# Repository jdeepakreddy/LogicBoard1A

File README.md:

## Full Documentation

I will amend this documentation as the project progresses.

**Logic Board 1 Variants:**

- Logic Board 1A (WiFi + BLE 5.0)
	- LB1A_DCA7M4_R512MB_F4GB (Dual Core A7 + M4, 512MB DDR3L RAM, 4GB eMMC)
	- LB1A_SCA7M4_R512MB_F4GB (Single Core A7 + M4, 512MB DDR3L RAM, 4GB eMMC)
- Logic Board 1B (Only WiFi)
	- LB1B_DCA7M4_R512MB_F4GB (Dual Core A7 + M4, 512MB DDR3L RAM, 4GB eMMC)
	- LB1B_SCA7M4_R512MB_F4GB (Single Core A7 + M4, 512MB DDR3L RAM, 4GB eMMC)
- Logic Board 1C (Only BLE 5.0)
	- LB1C_DCA7M4_R512MB_F4GB (Dual Core A7 + M4, 512MB DDR3L RAM, 4GB eMMC)
	- LB1C_SCA7M4_R512MB_F4GB (Single Core A7 + M4, 512MB DDR3L RAM, 4GB eMMC)
- Logic Board 1D (No wireless)
	- LB1D_DCA7M4_R512MB_F4GB (Dual Core A7 + M4, 512MB DDR3L RAM, 4GB eMMC)
	- LB1D_SCA7M4_R512MB_F4GB (Single Core A7 + M4, 512MB DDR3L RAM, 4GB eMMC)

**Logic Board I/O:**

Common expansion Board for all Logic Board 1 Variants. 

## A little background about the project

How it all started.

### Problem

While I was working on couple of popular linux dev boards like the BeagleBone Black and the Raspberry Pi, I've faced a few bunch of problems with both of them. Ofcourse, they are both fantastic boards to work with and they both have good community support, but, I are missing few things:

- **Raspberry Pi Compute Module 4 + IO Board**
    - CM4 is easy to use but not ideal for mass production.
    - No support for analog signals at hardware level.
    - Software PWM possible but not very precise.
    - Cannot support real time application or processing.
    - Not fully open-source and very minimum customization possible. <br>
<br>

- **BeagleBone Black**
    - Easy to use but user has to own build hardware for production.
    - PRUs make RT applications possible but super difficult to use.
    - Cannot support MIPI-DSI and HD graphics.
    - Programming PRUs is not an easy task.

### Solution

**Best of both worlds**

**Hello World STM32MP1 !!**

- Board design inspired from Raspberry Pi Compute Module 4 and CM4 IO board.
- Operating system derived from Beaglebone Black with implementation of Bonescript Library and Cloud9 IDE.
- Footprint compatible Single or dual Cortex-A7 Processors + dedicated Cortex-M4 core for real-time and low-power applications.
- Support for MIPI-DSI display for HMI applications.
- Fully open-source Hardware and Software.

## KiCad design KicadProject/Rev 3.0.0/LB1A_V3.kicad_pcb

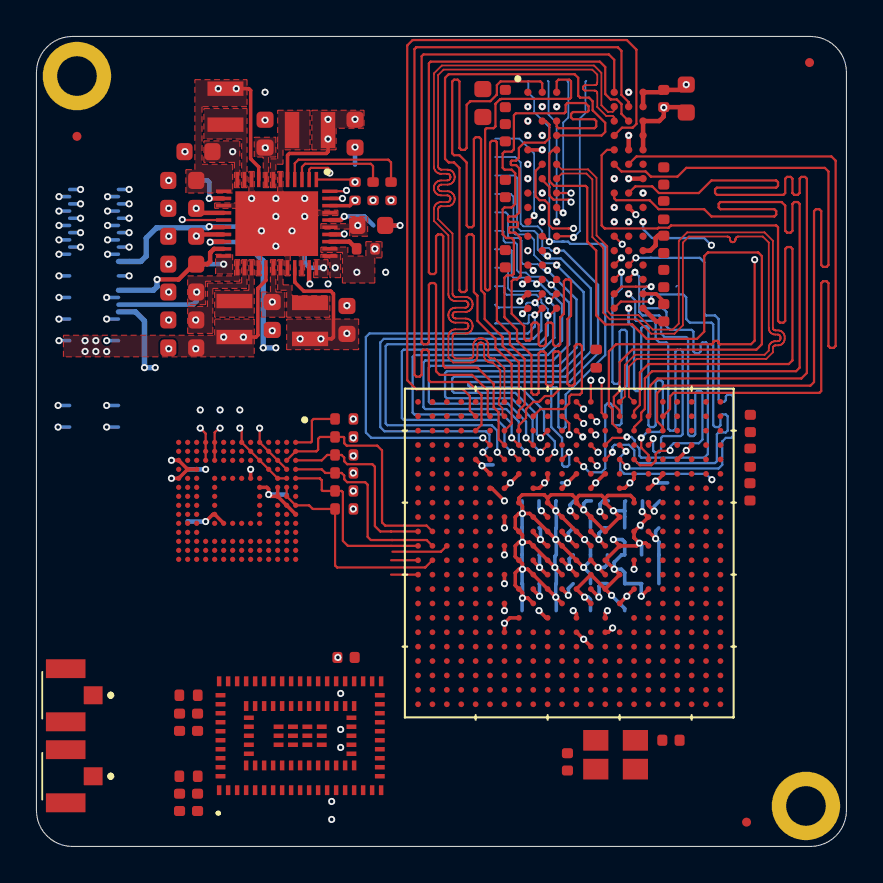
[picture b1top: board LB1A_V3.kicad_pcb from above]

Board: 6 copper layers, 45.0 x 45.0 mm, 188 parts (0 on the bottom side), 284 nets.

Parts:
C101, C105: 10nF; C_0402_1005Metric
C102, C103, C104: 10pF; C_0402_1005Metric
C201, C202, C203, C205, C206, C207, C208, C209, C210, C211, C212, C213, C214, C215, C216, C217, C218, C220, C221, C225, C226, C227, C228, C317, C325, C336, C337, C501, C502, C503, C504, C601, C607, C609: 100nF; C_0402_1005Metric
C223, C224, C401, C402, C403, C404, C405, C406, C407, C408, C412, C413, C414, C415, C416, C417: 10uF; C_0603_1608Metric
C229, C230, C409, C418, C419, C420, C421: 22uF; C_0603_1608Metric
C301, C302, C303, C304, C305, C306, C307, C308, C309, C310, C311, C312, C313, C314, C315, C316, C321, C322, C323, C324, C326, C327, C328, C329, C330, C331, C332, C333, C334, C335, C338, C339, C340, C341, C342: 1uF; C_0402_1005Metric
C410, C505, C506, C507, C606, C608: 4.7uF; C_0402_1005Metric
C411: 1uF; C_0603_1608Metric
C508: 2.2uF; C_0402_1005Metric
C602, C603, C604, C605: DNF; C_0402_1005Metric
FID701, FID702, FID703, FID704, FID705, FID706: Fiducial; Fiducial_0.5mm_Mask1.5mm
H701, H702: MountingHole_Pad; MountingHole_2.2mm_M2_DIN965_Pad
J601, J602: 2337019-1; 23370191
L401, L402, L403, L404: 1uH; MGV2520101R0M-10
R101: 3k; R_0402_1005Metric
R104, R105: 1k5; R_0402_1005Metric
R106, R221, R222, R501, R502, R503, R504, R505, R506, R507, R508, R509, R510, R603, R604, R605, R606, R607: 10k; R_0402_1005Metric
R201, R210: 240E; R_0402_1005Metric
R202, R203, R204, R205, R206, R207, R208, R209, R211, R212, R213, R214, R215, R216, R217, R218, R219, R220, R223, R224, R225, R227, R228, R229: 56E; R_0402_1005Metric
R226: 100E; R_0402_1005Metric
R301, R608: DNF; R_0402_1005Metric
R302, R401, R402, R601, R602: 0E; R_0402_1005Metric
U101: STM32MP157CAA3
U201: AS4C256M16D3LC-12BCN
U401: STPMIC1xPQR; STPMIC1BPQR
U501: S40FC004C1B2C00000
U601: LBEE59B1LV-278; LBEE59B1LV278
U701: DF40C-70DP-0.4V(51); DF40C70DP04V51
U702, U703: DF40C-100DP-0.4V(51); DF40C100DP04V51
X101: 32.768kHz; SiT1533AC-H5-DCC-32.768E
Y101: 24MHz; TSX3225240000MF10ZC3

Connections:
5V_VIN: C401.1, C402.1, C403.1, C404.1, C406.1, C407.1, C408.1, R401.2, R402.2, U401.8, U401.12, U401.19, U401.22, U401.24, U401.28, U401.36, U702.83, U702.84, U702.85, U702.86, U702.89, U702.90, U702.91, U702.92, U702.95, U702.96, U702.97, U702.98
/HSE_IN: C102.2, U101.T1, Y101.1
/HSE_OUT: C103.2, U101.T2, Y101.3
/LSE_IN: C104.1, U101.P1, X101.3
/MPU_DDR3L_Memory/DDR_A0: R202.2, U101.K19, U201.N3
/MPU_DDR3L_Memory/DDR_A1: R203.2, U101.M18, U201.P7
/MPU_DDR3L_Memory/DDR_A2: R204.2, U101.J18, U201.P3
/MPU_DDR3L_Memory/DDR_A3: R205.2, U101.J19, U201.N2
/MPU_DDR3L_Memory/DDR_A4: R206.2, U101.T18, U201.P8
/MPU_DDR3L_Memory/DDR_A5: R207.2, U101.H19, U201.P2
/MPU_DDR3L_Memory/DDR_A6: R208.2, U101.U19, U201.R8
/MPU_DDR3L_Memory/DDR_A7: R209.2, U101.F18, U201.R2
/MPU_DDR3L_Memory/DDR_A8: R211.2, U101.U18, U201.T8
/MPU_DDR3L_Memory/DDR_A9: R212.2, U101.H18, U201.R3
/MPU_DDR3L_Memory/DDR_A10: R213.2, U101.N18, U201.L7
/MPU_DDR3L_Memory/DDR_A11: R214.2, U101.P19, U201.R7
/MPU_DDR3L_Memory/DDR_A12: R215.2, U101.N19, U201.N7
/MPU_DDR3L_Memory/DDR_A13: R216.2, U101.G18, U201.T3
/MPU_DDR3L_Memory/DDR_A14: R217.2, U101.P18, U201.T7
/MPU_DDR3L_Memory/DDR_BA0: R218.2, U101.K20, U201.M2
/MPU_DDR3L_Memory/DDR_BA1: R219.2, U101.R18, U201.N8
/MPU_DDR3L_Memory/DDR_BA2: R220.2, U101.K18, U201.M3
/MPU_DDR3L_Memory/DDR_CASN: R225.2, U101.M22, U201.K3
/MPU_DDR3L_Memory/DDR_CKE: R222.2, R227.2, U101.R19, U201.K9
/MPU_DDR3L_Memory/DDR_CLK_N: R226.1, U101.N21, U201.K7
/MPU_DDR3L_Memory/DDR_CLK_P: R226.2, U101.N20, U201.J7
/MPU_DDR3L_Memory/DDR_CSN: R228.2, U101.L18, U201.L2
/MPU_DDR3L_Memory/DDR_DQ0: U101.E21, U201.D7
/MPU_DDR3L_Memory/DDR_DQ1: U101.F21, U201.A7
/MPU_DDR3L_Memory/DDR_DQ2: U101.H21, U201.A3
/MPU_DDR3L_Memory/DDR_DQ3: U101.E20, U201.B8
/MPU_DDR3L_Memory/DDR_DQ4: U101.J21, U201.C2
/MPU_DDR3L_Memory/DDR_DQ5: U101.H20, U201.C3
/MPU_DDR3L_Memory/DDR_DQ6: U101.H22, U201.A2
/MPU_DDR3L_Memory/DDR_DQ7: U101.G19, U201.C8
/MPU_DDR3L_Memory/DDR_DQ8: U101.N22, U201.F2
/MPU_DDR3L_Memory/DDR_DQ9: U101.R21, U201.E3
/MPU_DDR3L_Memory/DDR_DQ10: U101.P21, U201.G2
/MPU_DDR3L_Memory/DDR_DQ11: U101.T20, U201.H7
/MPU_DDR3L_Memory/DDR_DQ12: U101.V20, U201.F7
/MPU_DDR3L_Memory/DDR_DQ13: U101.R20, U201.H3
/MPU_DDR3L_Memory/DDR_DQ14: U101.U21, U201.H8
/MPU_DDR3L_Memory/DDR_DQ15: U101.V21, U201.F8
/MPU_DDR3L_Memory/DDR_DQM0: U101.G20, U201.D3
/MPU_DDR3L_Memory/DDR_DQM1: U101.T21, U201.E7
/MPU_DDR3L_Memory/DDR_DQS0_N: U101.G21, U201.B7
/MPU_DDR3L_Memory/DDR_DQS0_P: U101.G22, U201.C7
/MPU_DDR3L_Memory/DDR_DQS1_N: U101.R22, U201.G3
/MPU_DDR3L_Memory/DDR_DQS1_P: U101.T22, U201.F3
/MPU_DDR3L_Memory/DDR_ODT: R224.2, U101.L21, U201.K1
/MPU_DDR3L_Memory/DDR_RASN: R223.2, U101.M20, U201.J3
/MPU_DDR3L_Memory/DDR_RESETN: R221.2, U101.F19, U201.T2
/MPU_DDR3L_Memory/DDR_WEN: R229.2, U101.M21, U201.L3
ANA0: U101.R4, U703.84
ANA1: U101.T5, U703.83
BOOT0: U101.N3, U703.32
BOOT1: U101.N4, U703.33
BOOT2: U101.P4, U703.34
BT_DEV_WAKE: U101.H3, U601.29
BT_HOST_WAKE: U101.A2, U601.5
BT_PCM_CLK: U101.G2, U601.85
BT_PCM_SDI: U101.H5, U601.82
BT_PCM_SDO: U101.K5, U601.84
BT_PCM_WS: U101.F4, U601.83
BT_REG_ON: U101.G3, U601.9
BT_RF_OUT: C602.1, R601.2, U601.49
BT_USART3_CTS: U101.W1, U601.33
BT_USART3_RTS: U101.W12, U601.34
BT_USART3_RX: U101.AA7, U601.31
BT_USART3_TX: U101.V9, U601.32
DSI_CK_N: U101.A16, U703.95
DSI_CK_P: U101.B16, U703.96
DSI_D0_N: U101.A15, U703.99
DSI_D0_P: U101.B15, U703.100
DSI_D1_N: U101.A17, U703.97
DSI_D1_P: U101.B17, U703.98
GND: C101.2, C102.1, C103.1, C104.2, C105.2, C201.2, C202.2, C203.2, C205.2, C206.2, C207.2, C208.2, C209.2, C210.2, C211.2, C212.2, C213.2, C214.2, C215.2, C216.2, C217.2, C218.2, C220.2, C221.2, C223.2, C224.2, C225.2, C226.2, C227.2, C228.2, C229.2, C230.2, C301.2, C302.2, C303.2, C304.2, C305.2, C306.2, C307.2, C308.2, C309.2, C310.2, C311.2, C312.2, C313.2, C314.2, C315.2, C316.2, C317.2, C321.2, C322.2, C323.2, C324.2, C325.1, C326.2, C327.2, C328.2, C329.2, C330.2, C331.2, C332.2, C333.2, C334.2, C335.2, C336.2, C337.2, C338.2, C339.2, C340.2, C341.2, C342.2, C401.2, C402.2, C403.2, C404.2, C405.2, C406.2, C407.2, C408.2, C409.1, C410.2, C411.1, C412.1, C413.1, C414.1, C415.1, C416.1, C417.1, C418.2, C419.2, C420.2, C421.2, C501.2, C502.2, C503.2, C504.2, C505.2, C506.2, C507.2, C508.2, C601.2, C602.2, C603.2, C604.2, C605.2, C606.2, C607.2, C608.2, C609.2, H701.1, H702.1, J601.2, J601.3, J602.2, J602.3, R101.2, R201.2, R210.2, R221.1, R222.1, U101.A1, U101.A19, U101.A22, U101.AA4, U101.AA12, U101.AA13, U101.AA16, U101.AA18, U101.AB1, U101.AB18, U101.AB22, U101.B2, U101.B19, U101.C3, U101.C8, U101.C11, U101.C14, U101.C15, U101.C16, U101.C17, U101.C18, U101.C19, U101.C20, U101.D4, U101.D19, U101.E5, U101.E19, U101.F6, U101.F7, U101.F8, U101.F16, U101.F20, U101.G4, U101.G6, U101.G8, U101.G10, U101.G12, U101.G14, U101.G17, U101.H7, U101.J9, U101.J11, U101.J13, U101.J17, U101.J20, U101.K3, U101.K7, U101.K10, U101.K12, U101.K14, U101.L9, U101.L11, U101.L13, U101.L17, U101.L19, U101.L20, U101.M5, U101.M7, U101.M10, U101.M12, U101.M14, U101.N6, U101.N9, U101.N11, U101.N13, U101.N17, U101.P2, U101.P3, U101.P5, U101.P7, U101.P10, U101.P12, U101.P14, U101.P20, U101.R6, U101.R8, U101.R17, U101.T6, U101.T7, U101.T9, U101.T11, U101.T19, U101.U6, U101.U7, U101.U13, U101.U15, U101.U17, U101.U20, U101.V5, U101.V16, U101.V18, U101.V19, U101.W17, U101.W19, U101.Y3, U101.Y7, U101.Y10, U101.Y13, U101.Y14, U101.Y15, U101.Y18, U101.Y20, U201.A9, U201.B1, U201.B3, U201.B9, U201.D1, U201.D8, U201.E1, U201.E2, U201.E8, U201.F9, U201.G1, U201.G8, U201.G9, U201.J2, U201.J8, U201.M1, U201.M9, U201.P1, U201.P9, U201.T1, U201.T9, U401.6, U401.10, U401.15, U401.26, U401.30, U401.32, U401.41, U401.ep, U501.A6, U501.C4, U501.D3, U501.E2, U501.E7, U501.F1, U501.G5, U501.H10, U501.J5, U501.K8, U501.N2, U501.N5, U501.P1, U501.P4, U501.P6, U601.1, U601.2, U601.3, U601.6, U601.11, U601.15, U601.19, U601.20, U601.27, U601.30, U601.36, U601.47, U601.48, U601.50, U601.51, U601.52, U601.53, U601.57, U601.59, U601.60, U601.65, U601.72, U601.73, U601.94, U601.95, U601.96, U601.97, U601.98, U601.99, U601.100, U601.101, U601.102, U601.103, U601.104, U601.105, U601.106, U702.33, U702.34, U702.39, U702.40, U702.57, U702.58, U702.63, U702.64, U702.69, U702.70, U702.75, U702.76, U702.81, U702.82, U702.87, U702.88, U702.93, U702.94, U702.99, U702.100, X101.2, Y101.2, Y101.4
I2C4_SCL: R104.1, U101.G1, U401.4, U703.86
I2C4_SDA: R105.1, U101.H4, U401.3, U703.85
JTDI: U101.D16, U701.43
JTDO_TRACESWO: U101.E16, U701.42
JTRST: U101.E15, U701.41
LPO_32: U101.AB10, U601.80
MPU_VDDA_1V8_REG: C335.1, C336.1, U101.AB12, U101.B14
NRST: C101.1, R106.1, U101.R2, U401.1, U501.J1, U501.J2, U501.J3, U501.K5, U703.82
unnamed: C105.1, U101.R1
unnamed: C317.1, R301.1, R302.1, U101.M4
unnamed: C330.1, U101.AB17
unnamed: C342.1, U101.A18, U101.B18
unnamed: C409.2, U401.34
unnamed: C410.1, U401.40
unnamed: C508.1, U501.C1, U501.C2
unnamed: C603.1, J601.1, R601.1
unnamed: C604.1, R602.2, U601.58
unnamed: C605.1, J602.1, R602.1
unnamed: L401.1, U401.7
unnamed: L402.1, U401.11
unnamed: L403.1, U401.29
unnamed: L404.1, U401.25
unnamed: R101.1, U101.AA17
unnamed: R201.1, U201.L8
unnamed: R210.1, U101.K22
unnamed: R401.1, U401.33
unnamed: R402.1, U401.37
OTG_VBUS: U101.V15, U701.24
PA0_WAKEUP: U101.AA3, U401.43
PA1: U101.V4, U701.1
PA2: U101.AB2, U701.2
PA3: U101.T4, U701.3
PA4: U101.V6, U701.4
PA5: U101.U5, U701.5
PA6: U101.W9, U701.6
PA7: U101.Y9, U701.7
PA10: U101.Y17, U701.8
PA11: U101.Y16, U701.9
PA12: U101.W16, U701.10
PA13: U101.W3, U701.11
PA14: U101.R3, U701.12
PA15: U101.E11, U701.13
PB0: U101.AB5, U701.14
PB1: U101.AA5, U701.15
PB2: U101.V13, U701.16
PB5: U101.AA8, U701.17
PB6: U101.W13, U701.18
PB7: U101.F11, U701.19
PB8: U101.AB8, U701.20
PB9: U101.F12, U701.21
PB11: U101.Y5, U701.22
PB13: U101.V10, U701.23
PC0: U101.U10, U701.70
PC1: U101.AB3, U701.69
PC2: U101.Y1, U701.68
PC3: U101.U3, U701.67
PC4: U101.AB6, U701.66
PC5: U101.AA6, U701.65
PC6: U101.E13, U701.64
PC7: U101.D13, U701.63
PD0: U101.C10, U701.57
PD1: U101.B10, U701.56
PD4: U101.C9, U701.54
PD5: U101.A9, U701.53
PD6: U101.L3, U701.52
PD8: U101.M1, U701.51
PD9: U101.M2, U701.50
PD10: U101.A8, U701.49
PD11: U101.AB9, U701.48
PD13: U101.V14, U701.47
PD14: U101.M3, U701.46
PE0: U101.C5, U702.1
PE1: U101.D7, U702.2
PE2: U101.Y2, U702.3
PE4: U101.F15, U702.4
PE6: U101.E9, U702.5
PE7: U101.W10, U702.6
PE8: U101.Y12, U702.7
PE9: U101.W11, U702.8
PE10: U101.W14, U702.9
PE11: U101.D5, U702.10
PE12: U101.E4, U702.11
PE13: U101.A4, U702.12
PE14: U101.B4, U702.13
PE15: U101.C4, U702.14
PF2: U101.F13, U702.15
PF3: U101.V3, U702.16
PF6: U101.AA11, U702.17
PF7: U101.AA10, U702.18
PF9: U101.AB11, U702.19
PF10: U101.V12, U702.20
PF11: U101.W8, U702.21
PF12: U101.V8, U702.22
PF13: U101.W7, U702.23
PF14: U101.V7, U702.24
PF15: U101.W6, U702.25
PG0: U101.W5, U703.80
PG1: U101.Y4, U703.70
PG2: U101.W4, U703.79
PG3: U101.U4, U703.69
PG4: U101.AB4, U703.78
PG5: U101.U8, U703.68
PG7: U101.Y11, U703.77
PG8: U101.Y8, U703.67
PG9: U101.W15, U703.76
PG10: U101.AA9, U703.66
PG11: U101.U11, U703.75
PG12: U101.J4, U703.65
PG13: U101.AA1, U703.74
PG14: U101.AA2, U703.64
PH2: U101.AB7, U703.73
PH3: U101.Y6, U703.56
PH6: U101.V11, U703.72
PH7: U101.W2, U703.63
PH8: U101.D6, U703.71
PH9: U101.E6, U703.55
PH10: U101.B1, U703.62
PH11: U101.B3, U703.61
PH12: U101.F5, U703.60
PH13: U101.D3, U703.59
PH14: U101.C2, U703.58
PH15: U101.C1, U703.57
PI0: U101.D1, U703.1
PI1: U101.E2, U703.2
PI2: U101.E1, U703.3
PI3: U101.E3, U703.4
PI4: U101.J6, U703.5
PI5: U101.F2, U703.6
PI6: U101.G5, U703.7
PI7: U101.F1, U703.8
PI8: U101.N1, U703.9
PI9: U101.J5, U703.10
PI11: U101.T3, U703.11
PI12: U101.H2, U703.12
PI13: U101.H1, U703.13
PI14: U101.D2, U703.14
PI15: U101.F3, U703.15
PJ0: U101.J2, U703.16
PJ1: U101.L6, U703.17
PJ2: U101.K4, U703.18
PJ3: U101.J1, U703.19
PJ4: U101.K2, U703.20
PJ5: U101.K1, U703.21
PJ6: U101.L5, U703.22
PJ7: U101.H6, U703.23
PJ8: U101.L4, U703.24
PJ9: U101.J3, U703.25
PJ10: U101.L2, U703.26
PJ11: U101.K6, U703.27
PJ12: U101.B8, U703.28
PJ13: U101.A7, U703.29
PJ14: U101.B7, U703.30
PJ15: U101.C7, U703.31
PK0: U101.D8, U703.94
PK1: U101.E7, U703.93
PK2: U101.E8, U703.92
PK3: U101.B6, U703.91
PK4: U101.A6, U703.90
PK5: U101.C6, U703.89
PK6: U101.A5, U703.88
PK7: U101.B5, U703.87
PMIC_LDO1_1V8: C413.2, C606.1, C607.1, C608.1, C609.1, R603.1, R604.1, R605.1, R606.1, R607.1, R608.1, U401.23, U601.13, U601.14, U601.35, U702.65, U702.66, U702.67, U702.68
PMIC_LDO2_2V9: C415.2, U401.18, U702.77, U702.78, U702.79, U702.80
PMIC_LDO3_VTT_DDR: C203.1, C205.1, C206.1, C208.1, C209.1, C210.1, C211.1, C225.1, C226.1, C227.1, C228.1, C229.1, C230.1, C412.2, R202.1, R203.1, R204.1, R205.1, R206.1, R207.1, R208.1, R209.1, R211.1, R212.1, R213.1, R214.1, R215.1, R216.1, R217.1, R218.1, R219.1, R220.1, R223.1, R224.1, R225.1, R227.1, R228.1, R229.1, U401.14
PMIC_LDO4_VDD_USB: C337.1, C417.2, U101.AB13, U101.AB16, U401.39
PMIC_LDO5_2V9: C416.2, C501.1, C502.1, C503.1, C504.1, C505.1, C506.1, C507.1, R501.1, R502.1, R503.1, R504.1, R505.1, R506.1, R507.1, R508.1, R509.1, R510.1, U401.20, U501.A9, U501.B8, U501.C6, U501.C7, U501.E6, U501.F5, U501.J10, U501.K9, U501.M4, U501.N4, U501.P3, U501.P5, U702.35, U702.36, U702.37, U702.38
PMIC_LDO6_1V0: C414.2, U401.21, U702.71, U702.72, U702.73, U702.74
PMIC_VOUT1_VDD_CORE: C305.1, C306.1, C307.1, C308.1, C313.1, C314.1, C315.1, C316.1, C321.1, C322.1, C323.1, C324.1, C326.1, C327.1, C328.1, C329.1, C418.1, L401.2, U101.H9, U101.H11, U101.H13, U101.H15, U101.J8, U101.J10, U101.J12, U101.J14, U101.K9, U101.K11, U101.K13, U101.K15, U101.L8, U101.L10, U101.L12, U101.L14, U101.M11, U101.M13, U101.M15, U101.N12, U101.N14, U101.P13, U101.P15, U101.R14, U101.T15, U401.5
PMIC_VOUT2_VDD_DDR: C212.1, C213.1, C214.1, C215.1, C216.1, C217.1, C218.1, C220.1, C221.1, C223.1, C224.1, C331.1, C332.1, C333.1, C334.1, C338.1, C339.1, C340.1, C341.1, C405.1, C419.1, L402.2, U101.E18, U101.F17, U101.G16, U101.H17, U101.J16, U101.K17, U101.L16, U101.M17, U101.N16, U101.P17, U101.R16, U101.T17, U101.U16, U101.V17, U101.W18, U101.Y19, U201.A1, U201.A8, U201.B2, U201.C1, U201.C9, U201.D2, U201.D9, U201.E9, U201.F1, U201.G7, U201.H2, U201.H9, U201.K2, U201.K8, U201.N1, U201.N9, U201.R1, U201.R9, U401.9, U401.13
PMIC_VOUT3_VDD: C301.1, C302.1, C303.1, C304.1, C309.1, C310.1, C311.1, C312.1, C420.1, L403.2, R104.2, R105.2, R106.2, R302.2, U101.A14, U101.D18, U101.M6, U101.M9, U101.N5, U101.N8, U101.N10, U101.P9, U101.P11, U101.R5, U101.R10, U101.R12, U101.T13, U101.U2, U101.U9, U101.U12, U101.U14, U101.V2, U401.31, U401.42, X101.4
PMIC_VOUT4_3V3: C421.1, L404.2, U401.27, U702.51, U702.52, U702.53, U702.54, U702.55, U702.56, U702.59, U702.60, U702.61, U702.62
PMIC_VREF_DDR: C201.1, C202.1, C207.1, C411.2, U101.AB19, U201.H1, U201.M8, U401.16
PMIC_WAKEUP: U101.N2, U401.2
PONKEYn: U401.17, U703.81
POWER_ON: U101.V1, U401.44
SDMMC1_CK: U101.E12, U701.58
SDMMC1_CMD: U101.D12, U701.55
SDMMC1_D0: U101.E14, U701.62
SDMMC1_D1: U101.D14, U701.61
SDMMC1_D2: U101.F14, U701.60
SDMMC1_D3: U101.D15, U701.59
SDMMC2_CK: R509.2, U101.A10, U501.K1, U501.K2, U501.K3, U501.M6
SDMMC2_CMD: R510.2, U101.D11, U501.L1, U501.L2, U501.L3, U501.M5
SDMMC2_D0: R501.2, U101.A13, U501.A3
SDMMC2_D1: R502.2, U101.B12, U501.A4
SDMMC2_D2: R503.2, U101.A12, U501.A5
SDMMC2_D3: R504.2, U101.C13, U501.A1, U501.B2
SDMMC2_D4: R505.2, U101.B13, U501.A2, U501.B3
SDMMC2_D5: R506.2, U101.A11, U501.B4, U501.C3, U501.D2, U501.E1
SDMMC2_D6: R507.2, U101.C12, U501.B5, U501.C5, U501.D4, U501.E3, U501.F2, U501.G1
SDMMC2_D7: R508.2, U101.B11, U501.A8, U501.B6, U501.B7
SDMMC3_CK: R606.2, U101.D10, U601.24
SDMMC3_CMD: R608.2, U101.B9, U601.26
SDMMC3_D0: R605.2, U101.E10, U601.23
SDMMC3_D1: R604.2, U101.F9, U601.22
SDMMC3_D2: R603.2, U101.D9, U601.21
SDMMC3_D3: R607.2, U101.F10, U601.25
STLINK_SWCLK: U101.D17, U701.44
STLINK_SWDIO: U101.E17, U701.45
USB1_N: U101.AB15, U701.25
USB1_P: U101.AA15, U701.26
USB2_N: U101.AA14, U701.27
USB2_P: U101.AB14, U701.28
VDDA: C325.2, U101.P6
VDDOUT_VDDIO: C601.1, U601.4, U601.28
WL_HOST_WAKE: U101.L1, U601.7
WL_REG_ON: U101.A3, U601.10

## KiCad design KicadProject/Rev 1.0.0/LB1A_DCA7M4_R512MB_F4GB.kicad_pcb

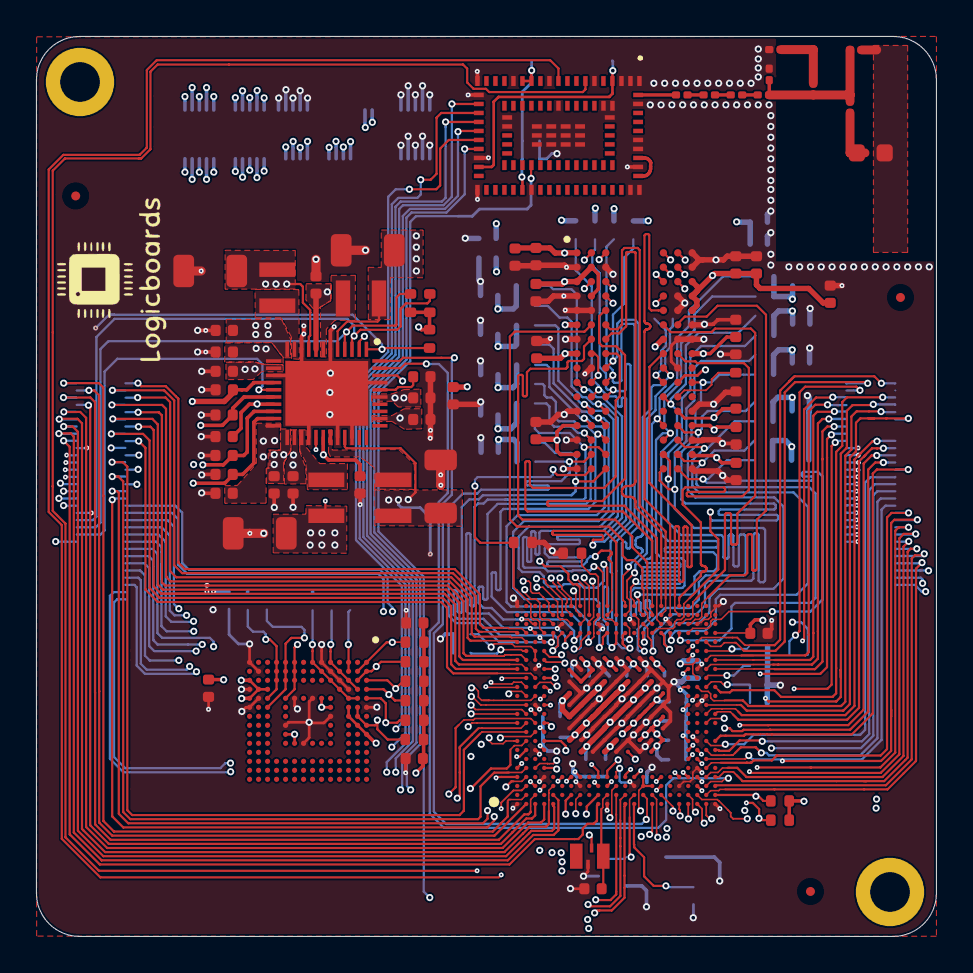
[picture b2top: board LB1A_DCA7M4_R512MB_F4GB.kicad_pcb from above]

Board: 6 copper layers, 50.0 x 50.0 mm, 156 parts (0 on the bottom side), 213 nets.

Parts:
C1, C2, C5, C6, C51, C52, C63, C64, C65, C66, C67, C68, C69, C70, C72, C73, C74: 1uF; C_0402_1005Metric
C3, C4, C8, C9, C10, C11, C12, C13, C14, C15, C16, C17, C18, C19, C20, C23, C24, C25, C26, C27, C28, C29, C30, C31, C32, C36, C37, C38, C39, C40, C79, C86: 100nF; C_0402_1005Metric
C7: 10nF; C_0402_1005Metric
C21, C22, C34, C35, C41, C43, C44, C45, C46, C54: 10uF; C_0402_1005Metric
C33: 0.3pF; C_0603_1608Metric
C42: 2.2uF; C_0402_1005Metric
C47, C48, C49, C50: 22uF; C_1206_3216Metric
C53, C55, C56, C57, C58, C59, C60, C61, C62, C85: 4.7uF; C_0402_1005Metric
C71: 0.3pF; C_0201_0603Metric
C75, C76, C77: 10pF; C_0402_1005Metric
C78: 2.0pF; C_0201_0603Metric
FID1, FID2, FID3, FID4, FID5, FID6: Fiducial; Fiducial_0.5mm_Mask1.5mm
H1, H3: MountingHole_Pad; MountingHole_2.2mm_M2_DIN965_Pad
L1, L2, L3, L4: 1uH; MGV2520101R0M-10
L5: 1.0nH; L_0201_0603Metric
L6: 3.0nH; L_0201_0603Metric
L7, L8: 1.5nH; L_0201_0603Metric
R1, R34: 240E; R_0402_1005Metric
R2, R3, R4, R5: 1k5; R_0402_1005Metric
R6, R27, R35, R46: 10k; R_0402_1005Metric
R7: 3k; R_0402_1005Metric
R8, R9, R10, R11, R12, R13, R14, R15, R16, R17, R18, R19, R20, R21, R22, R23, R24, R25, R28, R29, R30, R31, R32, R33: 56E; R_0402_1005Metric
R26: 100E; R_0402_1005Metric
R36, R37, R38, R39, R40, R41, R42, R43, R44, R45: 47k; R_0402_1005Metric
R47, R48, R49: 0E; R_0201_0603Metric
U1: TFBGA361_12X12; STM32MP157CAC3
U2: AS4C256M16D3LC-12BCN
U3: S40FC004C1B2C00000
U4: STPMIC1BPQR
U5, U6, U7: DF40C-70DP-0.4V(51); DF40C70DP04V51
U8: LBEE59B1LV-278; LBEE59B1LV278
X1: 32.768kHz; SiT1533AC-H5-DCC-32.768E
X2: 24MHz; TSX3225240000MF10ZC3

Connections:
5V_VIN: C43.1, C44.1, C45.1, C46.1, C51.1, C52.1, C53.1, U4.8, U4.12, U4.19, U4.22, U4.24, U4.28, U4.36, U6.2, U6.4, U6.6, U6.8, U6.10
ANA0: U1.U3, U7.31
ANA1: U1.U4, U7.33
ANT0: R49.1, U8.58
BOOT0: U1.N1, U5.37
BOOT1: U1.N4, U5.25
BOOT2: U1.M2, U5.41
BT_RF_IN: U8.49, U8.51
DDR_A0: R8.2, U1.L20, U2.N3
DDR_A1: R9.2, U1.P22, U2.P7
DDR_A2: R10.2, U1.J20, U2.P3
DDR_A3: R11.2, U1.K22, U2.N2
DDR_A4: R12.2, U1.V20, U2.P8
DDR_A5: R13.2, U1.H20, U2.P2
DDR_A6: R14.2, U1.W20, U2.R8
DDR_A7: R15.2, U1.E20, U2.R2
DDR_A8: R16.2, U1.Y20, U2.T8
DDR_A9: R17.2, U1.G20, U2.R3
DDR_A10: R18.2, U1.R22, U2.L7
DDR_A11: R19.2, U1.R20, U2.R7
DDR_A12: R20.2, U1.P23, U2.N7
DDR_A13: R21.2, U1.F20, U2.T3
DDR_A14: R22.2, U1.R21, U2.T7
DDR_BA0: R23.2, U1.L23, U2.M2
DDR_BA1: R24.2, U1.U20, U2.N8
DDR_BA2: R25.2, U1.M21, U2.M3
DDR_CASN: R33.2, U1.N20, U2.K3
DDR_CKE: R28.1, R35.2, U1.T20, U2.K9
DDR_CLK_N: R26.1, U1.N23, U2.K7
DDR_CLK_P: R26.2, U1.N22, U2.J7
DDR_CSN: R30.1, U1.M22, U2.L2
DDR_DQ0: U1.E22, U2.A2
DDR_DQ1: U1.F22, U2.C3
DDR_DQ2: U1.H21, U2.A7
DDR_DQ3: U1.E21, U2.C2
DDR_DQ4: U1.J21, U2.B8
DDR_DQ5: U1.J22, U2.C8
DDR_DQ6: U1.H22, U2.D7
DDR_DQ7: U1.G21, U2.A3
DDR_DQ8: U1.T21, U2.F2
DDR_DQ9: U1.U21, U2.E3
DDR_DQ10: U1.T22, U2.G2
DDR_DQ11: U1.W21, U2.F7
DDR_DQ12: U1.W23, U2.H8
DDR_DQ13: U1.T23, U2.H3
DDR_DQ14: U1.W22, U2.H7
DDR_DQ15: U1.Y21, U2.F8
DDR_DQM0: U1.H23, U2.D3
DDR_DQM1: U1.V22, U2.E7
DDR_DQS0_N: U1.G23, U2.B7
DDR_DQS0_P: U1.G22, U2.C7
DDR_DQS1_N: U1.U23, U2.G3
DDR_DQS1_P: U1.U22, U2.F3
DDR_ODT: R31.2, U1.L22, U2.K1
DDR_RASN: R29.2, U1.N21, U2.J3
DDR_RESETN: R27.2, U1.D20, U2.T2
DDR_WEN: R32.1, U1.M20, U2.L3
DSI_BL_CTRL: U1.AA19, U7.70
DSI_CKN: U1.A16, U5.56
DSI_CKP: U1.B16, U5.58
DSI_D0_N: U1.B15, U5.18
DSI_D0_P: U1.C15, U5.54
DSI_D1_N: U1.A17, U5.60
DSI_D1_P: U1.B17, U5.62
DSI_LCD_INT: U1.A14, U5.14
DSI_RESET: U1.D19, U5.36
DSI_TE: U1.B14, U5.16
ETH_CLK: U1.Y8, U7.48
ETH_CLK125: U1.Y6, U7.32
ETH_GTX_CLK: U1.AB2, U7.20
ETH_MDC: U1.AA6, U7.28
ETH_MDINT: U1.AC8, U7.46
ETH_MDIO: U1.AC3, U7.22
ETH_NRST: R6.1, U1.AC2, U7.18
ETH_RXD0: U1.AC7, U7.42
ETH_RXD1: U1.AB7, U7.38
ETH_RXD2: U1.AB6, U7.36
ETH_RXD3: U1.W4, U7.51
ETH_RX_CLK: U1.AA4, U7.16
ETH_RX_DV: U1.AB8, U7.44
ETH_TXD0: U1.AA2, U7.49
ETH_TXD1: U1.AA1, U7.43
ETH_TXD2: U1.Y2, U7.41
ETH_TXD3: U1.Y1, U7.39
ETH_TX_EN: U1.AB1, U7.45
GND: C1.2, C2.2, C3.2, C4.2, C5.1, C6.2, C7.2, C8.2, C9.2, C10.2, C11.2, C12.2, C13.2, C14.2, C15.2, C16.2, C17.2, C18.2, C19.2, C20.2, C21.2, C22.2, C23.2, C24.2, C25.2, C26.2, C27.2, C28.2, C29.2, C30.2, C31.2, C32.1, C34.2, C35.2, C36.2, C37.2, C38.2, C39.2, C40.2, C41.2, C42.2, C43.2, C44.2, C45.2, C46.2, C47.2, C48.2, C49.2, C50.2, C51.2, C52.2, C53.2, C54.2, C55.2, C56.2, C57.2, C58.2, C59.2, C60.2, C61.2, C62.2, C63.2, C64.2, C65.2, C66.2, C67.2, C68.2, C69.2, C70.2, C72.2, C73.2, C74.2, C75.1, C76.1, C77.1, C79.1, C85.2, C86.1, L8.2, R1.2, R7.2, R27.1, R34.2, R35.1, R47.1, U1.1A3, U1.1A5, U1.1A7, U1.1B2, U1.1B4, U1.1B6, U1.1B8, U1.1C1, U1.1C3, U1.1C5, U1.1C7, U1.1C9, U1.1D2, U1.1D4, U1.1D6, U1.1D8, U1.1E1, U1.1E3, U1.1E5, U1.1E7, U1.1E9, U1.1F2, U1.1F4, U1.1F6, U1.1F8, U1.1G1, U1.1G3, U1.1G5, U1.1G7, U1.1G9, U1.1H2, U1.1H4, U1.1H6, U1.1H8, U1.1J3, U1.1J5, U1.1J7, U1.A1, U1.A23, U1.AA5, U1.AA8, U1.AA12, U1.AA16, U1.AA21, U1.AB13, U1.AC1, U1.AC23, U1.C7, U1.C12, U1.C16, U1.C21, U1.D4, U1.F21, U1.H3, U1.K21, U1.L1, U1.P3, U1.P21, U1.V21, U1.W3, U2.A9, U2.B1, U2.B3, U2.B9, U2.D1, U2.D8, U2.E1, U2.E2, U2.E8, U2.F9, U2.G1, U2.G8, U2.G9, U2.J2, U2.J8, U2.M1, U2.M9, U2.P1, U2.P9, U2.T1, U2.T9, U3.A6, U3.C4, U3.D3, U3.E2, U3.E7, U3.F1, U3.G5, U3.H10, U3.J5, U3.K8, U3.N2, U3.N5, U3.P1, U3.P4, U3.P6, U4.6, U4.10, U4.15, U4.26, U4.30, U4.32, U4.41, U4.ep, U6.27, U6.29, U6.31, U6.33, U6.35, U6.61, U6.62, U6.63, U6.64, U6.65, U6.66, U6.67, U6.68, U6.69, U6.70, U8.1, U8.2, U8.3, U8.6, U8.11, U8.15, U8.19, U8.20, U8.27, U8.30, U8.36, U8.47, U8.48, U8.50, U8.52, U8.53, U8.57, U8.59, U8.60, U8.65, U8.72, U8.73, U8.94, U8.95, U8.96, U8.97, U8.98, U8.99, U8.100, U8.101, U8.102, U8.103, U8.104, U8.105, U8.106, X1.2, X2.2, X2.4
HDMI_CEC: U1.Y14, U7.53
HDMI_INT: U1.W1, U7.37
HDMI_NRST: U1.Y17, U7.65
I2C1_SCL: R2.1, U1.Y18, U7.67
I2C1_SDA: R3.1, U1.Y4, U7.47
I2C4_SCL: R4.1, U1.G2, U4.4, U5.29
I2C4_SDA: R5.1, U1.H2, U4.3, U5.31
I2S2_CK: U1.D14, U5.24
I2S2_SDO: U1.E1, U5.57
I2S2_WS: U1.B10, U5.50
JTCK_SWCLK: U1.B20, U5.70
JTDI: U1.A20, U5.68
JTDO_TRACESWO: U1.A19, U5.64
JTMS_SWDIO: U1.C20, U5.34
LCD_B0: U1.K1, U5.53
LCD_B1: U1.K4, U5.45
LCD_B2: U1.AB11, U7.54
LCD_B3: U1.B5, U5.44
LCD_B4: U1.B4, U5.42
LCD_B5: U1.U2, U7.35
LCD_B6: U1.F4, U5.51
LCD_B7: U1.K3, U5.43
LCD_CLK: U1.AC14, U7.66
LCD_DE: U1.Y12, U7.50
LCD_G0: U1.AA7, U7.30
LCD_G1: U1.C10, U5.52
LCD_G2: U1.D1, U5.61
LCD_G3: U1.C3, U5.40
LCD_G4: U1.B1, U5.67
LCD_G5: U1.C1, U5.63
LCD_G6: U1.E3, U5.59
LCD_G7: U1.E2, U5.55
LCD_HSYNC: U1.T1, U7.27
LCD_R0: U1.AB4, U7.26
LCD_R1: U1.AA3, U7.14
LCD_R2: U1.D5, U5.12
LCD_R3: U1.C5, U5.10
LCD_R4: U1.C2, U5.65
LCD_R5: U1.AB5, U7.34
LCD_R6: U1.B2, U5.69
LCD_R7: U1.D3, U5.38
LCD_VSYNC: U1.H4, U5.47
LPO_32: U1.L4, U8.80
MPU_VDDA_1V8_REG: C1.1, C4.1, U1.AB14, U1.C14
NJRST: U1.B19, U5.66
NRST: R46.2, U1.M3, U3.J1, U3.J2, U3.J3, U3.K5, U4.1, U5.33
unnamed: C5.2, U1.C17, U1.C18
unnamed: C6.1, U1.AB15
unnamed: C7.1, U1.M4
unnamed: C33.1, L5.2
unnamed: C33.2, C71.2
unnamed: C42.1, U3.C1, U3.C2
unnamed: C62.1, U4.40
unnamed: C71.1, C78.1, L5.1, L6.2, L8.1
unnamed: C75.2, U1.P2, X2.3
unnamed: C76.2, U1.P1, X2.1
unnamed: C77.2, U1.L2, X1.3
unnamed: C78.2, L7.1
unnamed: L1.1, U4.7
unnamed: L2.1, U4.11
unnamed: L3.1, U4.29
unnamed: L4.1, U4.25
unnamed: L6.1, R47.2
unnamed: L7.2, R48.2
unnamed: R1.1, U1.K23
unnamed: R7.1, U1.AB18
unnamed: R34.1, U2.L8
unnamed: R48.1, R49.2
PA0_WKUP: U1.AB3, U4.43
PMIC_LDO1_1V8: C56.1, C79.2, C85.1, C86.2, U4.23, U6.16, U6.18, U6.20, U6.22, U6.24, U8.13, U8.14, U8.35
PMIC_LDO2_2V9: C57.1, U4.18, U6.30, U6.32, U6.34, U6.36
PMIC_LDO3_VTT_DDR: C9.1, C10.1, C11.1, C12.1, C13.1, C14.1, C15.1, C16.1, C17.1, C18.1, C19.1, C20.1, C21.1, C22.1, C58.1, R8.1, R9.1, R10.1, R11.1, R12.1, R13.1, R14.1, R15.1, R16.1, R17.1, R18.1, R19.1, R20.1, R21.1, R22.1, R23.1, R24.1, R25.1, R28.2, R29.1, R30.2, R31.1, R32.2, R33.1, U4.14
PMIC_LDO4_VDD_USB: C3.1, C59.1, U1.AA15, U1.AA17, U4.39
PMIC_LDO5_2V9: C38.1, C39.1, C40.1, C41.1, C60.1, R36.1, R37.1, R38.1, R39.1, R40.1, R41.1, R42.1, R43.1, R44.1, R45.1, U3.A9, U3.B8, U3.C6, U3.C7, U3.E6, U3.F5, U3.J10, U3.K9, U3.M4, U3.N4, U3.P3, U3.P5, U4.20, U6.51, U6.53
PMIC_LDO6_1V0: C61.1, U4.21, U6.42, U6.44, U6.46, U6.48
PMIC_VOUT1_VDD_CORE: C47.1, C63.1, C64.1, C65.1, C66.1, L1.2, U1.1A2, U1.1A4, U1.1A6, U1.1B1, U1.1B3, U1.1B5, U1.1C2, U1.1C4, U1.1C6, U1.1D1, U1.1D3, U1.1D5, U1.1D7, U1.1E2, U1.1E4, U1.1E6, U1.1F5, U1.1F7, U1.1G6, U1.1H7, U4.5
PMIC_VOUT2_VDD_DDR: C23.1, C24.1, C25.1, C26.1, C27.1, C28.1, C29.1, C30.1, C31.1, C34.1, C35.1, C48.1, C54.1, C72.1, C73.1, C74.1, L2.2, U1.1A8, U1.1B7, U1.1B9, U1.1C8, U1.1D9, U1.1E8, U1.1F9, U1.1G8, U1.1H9, U1.1J8, U2.A1, U2.A8, U2.B2, U2.C1, U2.C9, U2.D2, U2.D9, U2.E9, U2.F1, U2.G7, U2.H2, U2.H9, U2.K2, U2.K8, U2.N1, U2.N9, U2.R1, U2.R9, U4.9, U4.13
PMIC_VOUT3_VDD: C2.1, C49.1, C67.1, C68.1, C69.1, C70.1, L3.2, R2.2, R3.2, R4.2, R5.2, R6.2, R46.1, U1.1F1, U1.1F3, U1.1G2, U1.1G4, U1.1H1, U1.1H3, U1.1H5, U1.1J2, U1.1J4, U1.1J6, U1.B18, U1.R3, U1.R4, U1.T3, U4.31, U4.42, U6.15, U6.17, U6.19, U6.21, U6.23, X1.4
PMIC_VOUT4_3V3: C50.1, L4.2, U4.27, U6.1, U6.3, U6.5, U6.7, U6.9
PMIC_VREF_DDR: C8.1, C36.1, C37.1, C55.1, U1.AC20, U2.H1, U2.M8, U4.16
PMIC_WAKEUP: U1.K2, U4.2
POWER_ON: U1.R2, U4.44
SDMMC1_CK: U1.D13, U5.22
SDMMC1_CMD: U1.D12, U5.20
SDMMC1_D0: U1.D18, U5.32
SDMMC1_D1: U1.D17, U5.30
SDMMC1_D2: U1.D15, U5.26
SDMMC1_D3: U1.D16, U5.28
SDMMC2_CK: R45.2, U1.C9, U3.K1, U3.K2, U3.K3, U3.M6
SDMMC2_CMD: R44.2, U1.A10, U3.L1, U3.L2, U3.L3, U3.M5
SDMMC2_D0: R36.2, U1.C13, U3.A3
SDMMC2_D1: R37.2, U1.B12, U3.A4
SDMMC2_D2: R38.2, U1.A11, U3.A5
SDMMC2_D3: R39.2, U1.B13, U3.A1, U3.B2
SDMMC2_D4: R40.2, U1.AB10, U3.A2, U3.B3
SDMMC2_D5: R41.2, U1.A8, U3.B4, U3.C3, U3.D2, U3.E1
SDMMC2_D6: R42.2, U1.C11, U3.B5, U3.C5, U3.D4, U3.E3, U3.F2, U3.G1
SDMMC2_D7: R43.2, U1.B11, U3.A8, U3.B6, U3.B7
SDMMC3_CK: U1.B7, U8.24
SDMMC3_CMD: U1.A5, U8.26
SDMMC3_D0: U1.D8, U8.23
SDMMC3_D1: U1.D9, U8.22
SDMMC3_D2: U1.D7, U8.21
SDMMC3_D3: U1.D10, U8.25
SPI5_MISO: U1.AC11, U7.52
SPI5_MOSI: U1.AA14, U7.62
SPI5_NSS: U1.AA13, U7.64
SPI5_SCK: U1.AB12, U7.60
STLINK_UART4_RX: U1.B8, U5.46
STLINK_UART4_TX: U1.B9, U5.48
STUSB1600_IRQOUTn: U1.P4, U7.25
USART1_CTS: U1.G4, U5.49
USART1_RTS: U1.AB19, U7.69
USART1_RX: U1.Y16, U7.55
USART1_TX: U1.Y7, U7.40
USB_DM1: U1.AB17, U7.63
USB_DM2: U1.AB16, U7.59
USB_DP1: U1.AC17, U7.61
USB_DP2: U1.AC16, U7.57
U_BUTTON_1: U1.N2, U5.39
U_BUTTON_2: U1.T2, U7.29
U_LED_1: U1.L3, U5.35
U_LED_2: U1.AC4, U7.24
VDDOUT_VDDIO: C32.2, U8.4, U8.28
WL_HOST_WAKE: U1.A4, U8.7
WL_REG_ON: U1.B3, U8.10
nPONKEY: U4.17, U5.27

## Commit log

2021-06-26 Schematic Finalized
2021-06-28 Design Complete
2021-06-28 Generated Fab Files
2021-07-06 Fabrications files added
2021-07-12 added documentation
2021-07-12 removed documentation
2021-07-13 added assembly diagrams
2021-07-13 added BOM
2021-07-26 v2 initial commit
2021-07-31 working on rev2 sch
2021-07-31 mpu memory
2021-07-31 mpu power sch
2021-07-31 pmic sch
2021-07-31 emmc flash sch
2021-07-31 wx sch
2021-07-31 ERC done
2021-07-31 schematic outputs added
2021-08-01 verfication 1 complete
2021-08-02 verification complete
2021-08-02 annotated sch
2021-08-02 assigned footprints
2021-08-02 modified wx sch
2021-08-02 BT_RF_IN pin connected to ground
2021-08-02 just before starting placement
2021-08-03 V3 initial commit
2021-08-03 working on MPU
2021-08-03 only b2b connectors left
2021-08-03 still working on connectors
2021-08-04 verification pending and connectors
2021-08-04 sch verification complete
2021-08-04 sch pdf 1st version
2021-08-04 working on placement
2021-08-05 working on pmic layout
2021-08-05 Updated location of PMIC
2021-08-05 pmic placement 1
2021-08-05 pmic placement 2
2021-08-05 pmic placement 3
2021-08-05 pmic complete
2021-08-05 eMMC also done
2021-08-05 wireless module placement
2021-08-05 working on mpu placement
2021-08-06 working on mpu placements
2021-08-06 mcu vdd_core decoupling completed
2021-08-06 mpu vdd complete
2021-08-06 mpu connections
2021-08-06 mpu vdd_ddq done
2021-08-06 mpu another commit
2021-08-07 mpu done
2021-08-07 working on DDR placement
2021-08-07 all components placed
2021-08-07 started routing
2021-08-07 working on routing pmic
2021-08-07 still working on pmic routing
2021-08-07 working on power routing
2021-08-07 working on power
2021-08-09 changed placement and components
2021-08-09 added 3d models
2021-08-09 working on system power routing
2021-08-09 pmic power routing complete
2021-08-09 pmic power complete
2021-08-09 redesigning power
2021-08-09 still working on power
2021-08-10 working on power route
2021-08-10 still working
2021-08-10 pmic only completed
2021-08-10 pmic improved
2021-08-10 5v_in connected to PMIC
2021-08-10 working on connectors
2021-08-10 flash routing done
2021-08-10 wx power done
2021-08-10 adjusted flash power
2021-08-10 again adjusted flash power plane
2021-08-10 working on vdd
2021-08-10 power complete adjustments left
2021-08-10 tidying
2021-08-10 little more tidy
2021-08-11 ddr3l routing
2021-08-11 moved ram a bit to the right
2021-08-11 moved ram little more
2021-08-11 some routed
2021-08-11 a little completed
2021-08-11 more ddr3l routing
2021-08-12 2 more traces left on top
2021-08-12 top layer of ddr3l complete
2021-08-12 working on ddr3l
2021-08-13 some updates on ram routing
2021-08-13 ddr3l cleaning required
2021-08-13 some cleaning done
2021-08-13 little more done
2021-08-13 some more traces done
2021-08-13 updated ram routing
2021-08-13 updated pcb routing near ram
2021-08-14 some more connections
2021-08-20 some changes in view
2021-08-24 updating ram traces
2021-08-25 updating traces on ram
2021-08-25 updated traces
2021-08-25 updating ram routes
2021-08-25 some more routing
2021-08-25 updating routes
2021-08-25 updated ram routings
2021-08-26 routing

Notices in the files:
parts and their libraries:
Copyright 2016 Accelerated Designs. All rights reserved.
Copyright 2021 Accelerated Designs. All rights reserved.
